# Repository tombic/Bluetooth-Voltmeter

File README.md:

# Bluetooth-Voltmeter
Arduino + BTM-112 module that send voltage over bluetooth serial link. Using common Metex voltmeter protocol, it is compatible with software that can read this protocol, e.g.  SmuView.

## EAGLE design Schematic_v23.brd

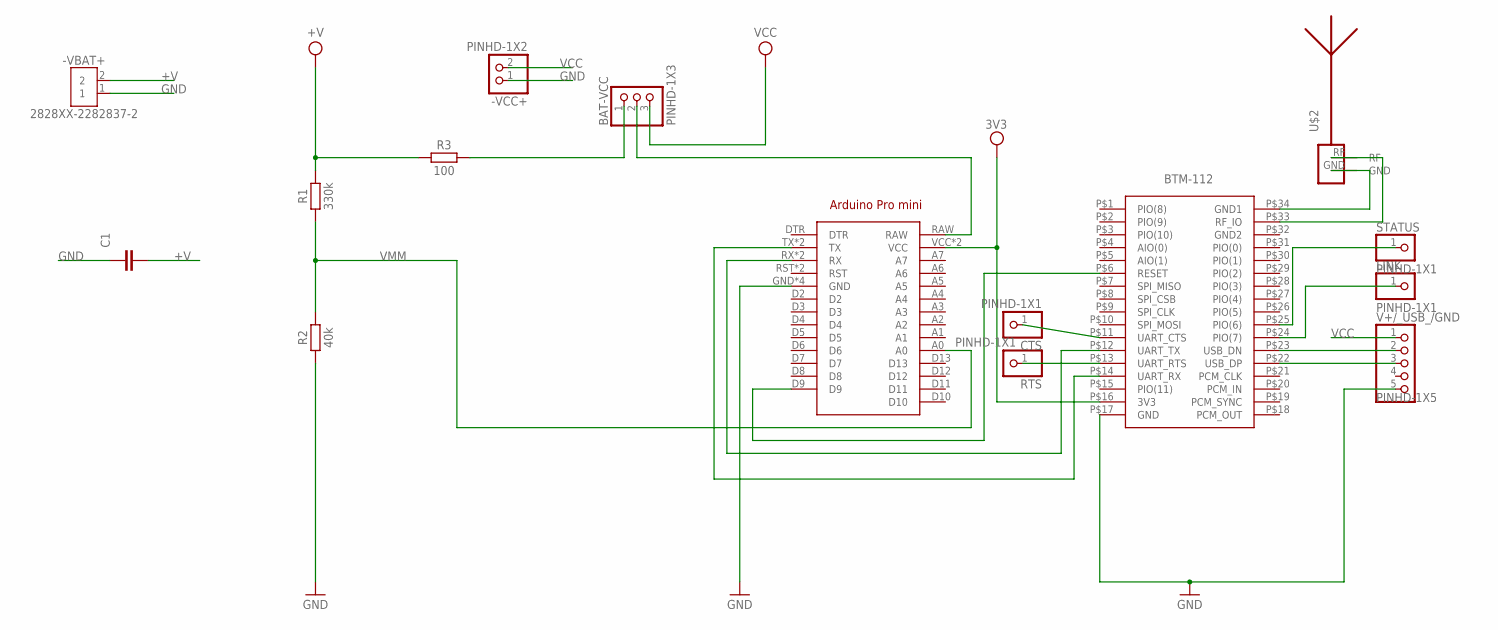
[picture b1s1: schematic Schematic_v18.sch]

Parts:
-VBAT+: 2828XX-2282837-2; TERMBLK_508-2N
-VCC+: PINHD-1X2; 1X02
ARDUINO1: ARDUINO_PRO_MINI
BAT-VCC: PINHD-1X3; 1X03
C1: C_RADIAL-12.5MM-DIA; CAPRD550W60D1025H1250B
CTS: PINHD-1X1; 1X01
LINK: PINHD-1X1; 1X01
R1: 330k; RESAD724W46L381D178B
R2: 40k; RESAD724W46L381D178B
R3: 100; RESAD724W46L381D178B
RTS: PINHD-1X1; 1X01
STATUS: PINHD-1X1; 1X01
U$1: BTM-112
U$2: ANTENNA_1RIGHT; SWRA117D_RIGHT
V+/_USB_/GND: PINHD-1X5; 1X05

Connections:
3V3: ARDUINO1.VCC, ARDUINO1.VCC@1 (VCC), U$1.P$16 (3V3)
+V: -VBAT+.2, C1.2, R1.2, R3.1
CTS: CTS.1, U$1.P$11 (UART_CTS)
GND: -VBAT+.1, -VCC+.1, ARDUINO1.GND, ARDUINO1.GND@1 (GND), ARDUINO1.GND@2 (GND), ARDUINO1.GND@3 (GND), C1.1, R2.1, U$1.P$17 (GND), V+/_USB_/GND.5
GND2: U$1.P$32 (GND2)
unnamed: U$1.P$33 (RF_IO), U$2.RF
unnamed: U$1.P$34 (GND1), U$2.GND
unnamed: ARDUINO1.RX, ARDUINO1.RX@1 (RX), U$1.P$12 (UART_TX)
unnamed: ARDUINO1.TX, ARDUINO1.TX@1 (TX), U$1.P$14 (UART_RX)
unnamed: ARDUINO1.RAW, BAT-VCC.2
unnamed: ARDUINO1.D9, U$1.P$6 (RESET)
unnamed: BAT-VCC.1, R3.2
unnamed: U$1.P$23 (USB_DN), V+/_USB_/GND.2
unnamed: U$1.P$22 (USB_DP), V+/_USB_/GND.3
unnamed: LINK.1, U$1.P$24 (PIO(7))
unnamed: STATUS.1, U$1.P$25 (PIO(6))
RTS: RTS.1, U$1.P$13 (UART_RTS)
VCC: -VCC+.2, BAT-VCC.3, V+/_USB_/GND.1
VMM: ARDUINO1.A0, R1.1, R2.2

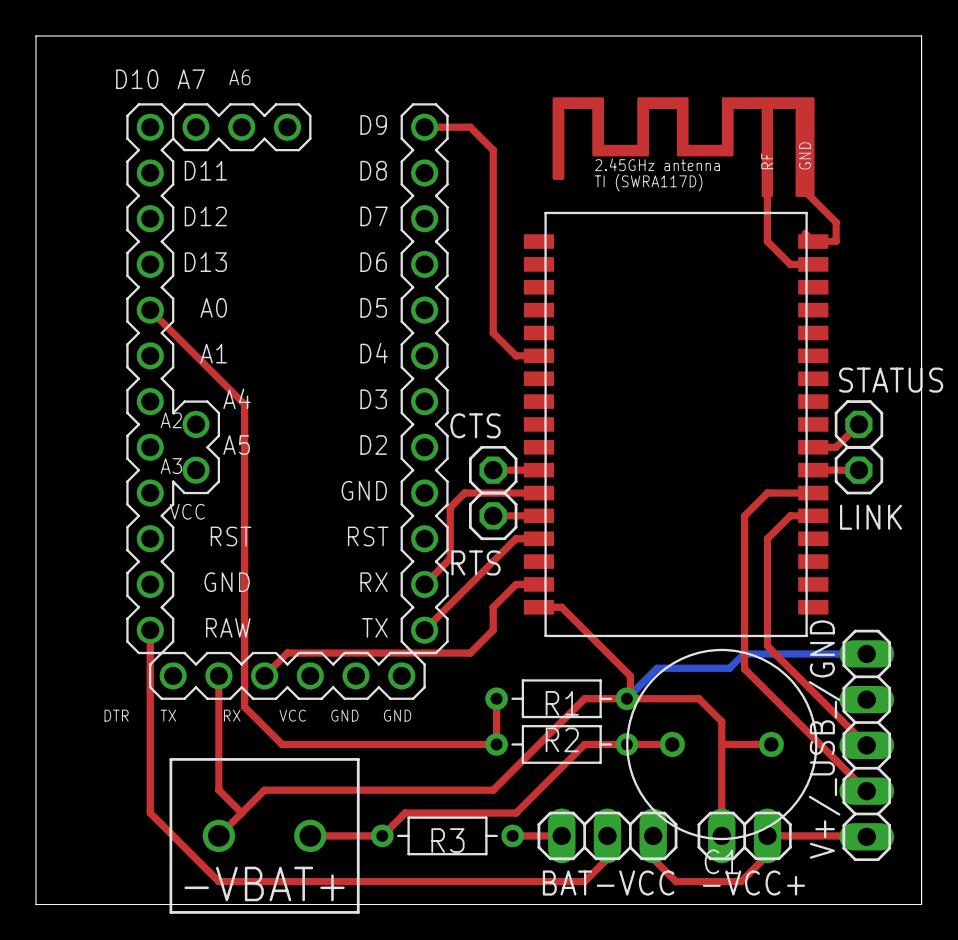
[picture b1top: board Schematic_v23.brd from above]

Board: 2 copper layers, 49.2 x 48.2 mm, 15 parts (0 on the bottom side), 18 nets.
